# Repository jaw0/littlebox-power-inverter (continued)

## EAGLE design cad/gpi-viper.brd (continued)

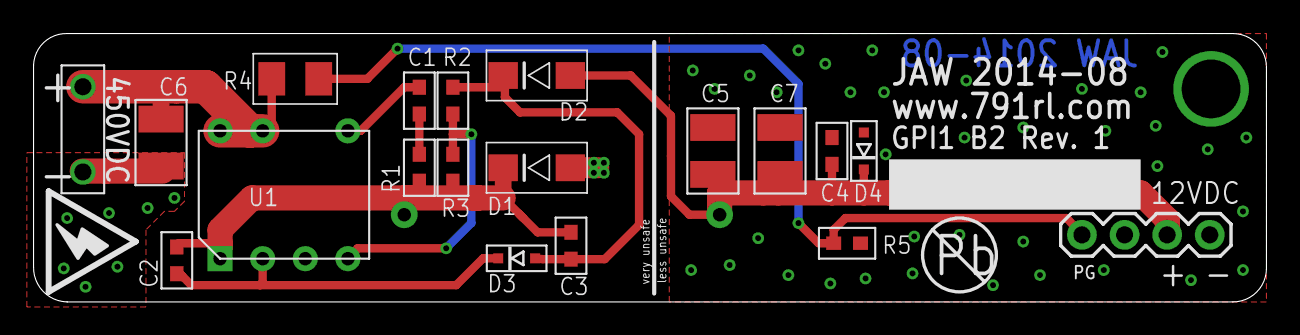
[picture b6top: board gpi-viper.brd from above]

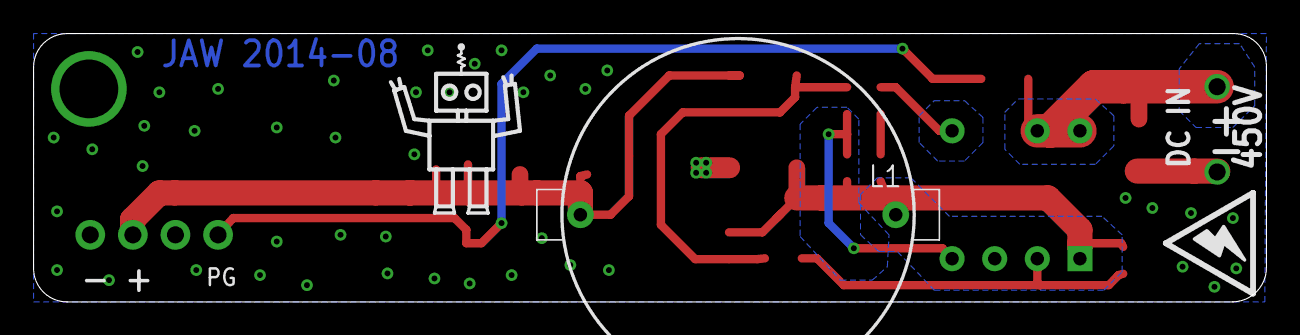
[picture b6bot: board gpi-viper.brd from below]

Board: 2 copper layers, 73.5 x 16.0 mm, 23 parts (3 on the bottom side), 10 nets.

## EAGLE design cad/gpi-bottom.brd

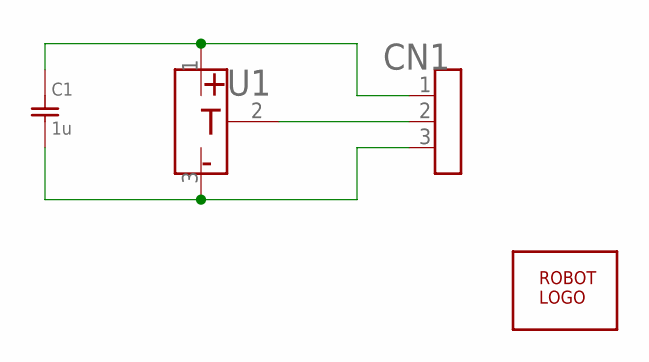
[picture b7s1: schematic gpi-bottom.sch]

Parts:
C1: 1u; SMD0603
CN1: HEADER-3X12MM; HEADER-3X1-2SMD
U1: TEMPERATURE; SOT-23
U$1: ROBOTMAN-LOGO

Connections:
unnamed: C1.1, CN1.1, U1.1 (V)
unnamed: CN1.2, U1.2 (OUT)
unnamed: C1.2, CN1.3, U1.3 (G)

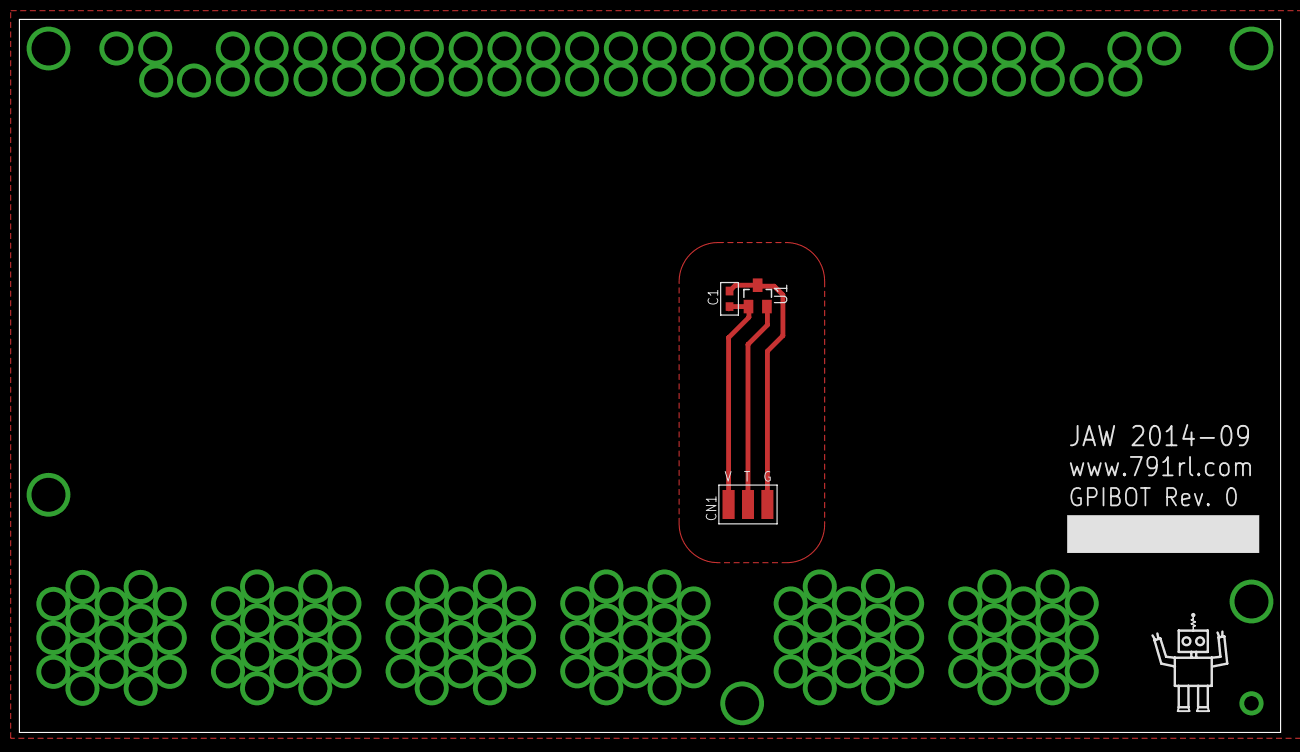
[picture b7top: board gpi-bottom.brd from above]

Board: 2 copper layers, 130.0 x 73.5 mm, 4 parts (0 on the bottom side), 3 nets.

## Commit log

2014-08-10 boards rev 0
2014-08-12 regulator
2014-08-12 tweak
2014-08-12 better output filter
2014-08-13 tweak sent to fab
2014-08-23 viper package
2014-08-24 viper26, clearances, diodes
2014-09-04 code
2014-09-04 tweak text
2014-09-05 adc, init
2014-09-06 gate snubbers
2014-09-07 op-amps on v-divs
2014-09-07 temp sensor
2014-09-07 op amp on v-div
2014-09-07 vcca to conn
2014-09-07 sync, green led
2014-09-07 labels
2014-09-08 zoned grounds
2014-09-09 planes
2014-09-11 lmp current sense
2014-09-11 swap layers
2014-09-11 filter
2014-09-14 output filter
2014-09-16 move leds, hole size
2014-09-17 corners
2014-10-11 control loops
2014-10-12 missing wire
2014-10-12 bigger cap
2014-10-13 diode silk
2014-10-15 burst mode
2014-10-15 no burst mode
2014-10-18 stats
2014-10-18 vh oscillates
2014-10-18 caps
2014-10-18 works. itarg converges slowly
2014-10-19 seems good
2014-10-19 calibrate
2014-10-19 dc out
2014-10-20 clean
2014-10-25 adj freq to avoid saturation
2014-10-25 calc
2015-06-26 comments
2015-12-23 pdfs, comments
2015-12-23 add files
2016-03-11 revert opamp, tweak
2016-03-12 rename files
2016-03-12 add images
2016-03-12 add schematic pdf
2016-03-12 add readme
2016-03-13 comment
2016-03-13 readme, clean
2016-03-13 rename
2016-03-13 moved pdfs to img/
2021-11-11 added table for 50hz operation
